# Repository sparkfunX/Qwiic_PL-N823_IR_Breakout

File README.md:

SparkFun PL-N823 IR Breakout
===================================

[*SparkFun Qwiic IR Breakout (SPX-15804)*](https://www.sparkfun.com/products/15804)

PL-N823-01 Lensless IR Sensor breakout with signal amplifier and I2C ADC 

This board allows for digital sensor reading of IR signals from external sources. One such application can be the detection of heat given off by the human body. Operating voltage is 5V for the board as a whole, and while under 1mm thick materials detection can be as far away as 10cm to 20cm.

Repository contents
-------------------

* **/Documents** - Contains datasheets
* **/Hardware** - Current .brd and .sch files for product

Documentation
-------------

* **[Installing an Arduino Library Guide](https://learn.sparkfun.com/tutorials/installing-an-arduino-library)** - Basic information on how to install an Arduino library.

License Information
-------------------

This product is _**open source**_!

Please review the LICENSE.md file for license information.

If you have any questions or concerns on licensing, please contact technical support on our [SparkFun forums](https://forum.sparkfun.com/viewforum.php?f=152).

Distributed as-is; no warranty is given.

- Your friends at SparkFun.

_<COLLABORATION CREDIT>_

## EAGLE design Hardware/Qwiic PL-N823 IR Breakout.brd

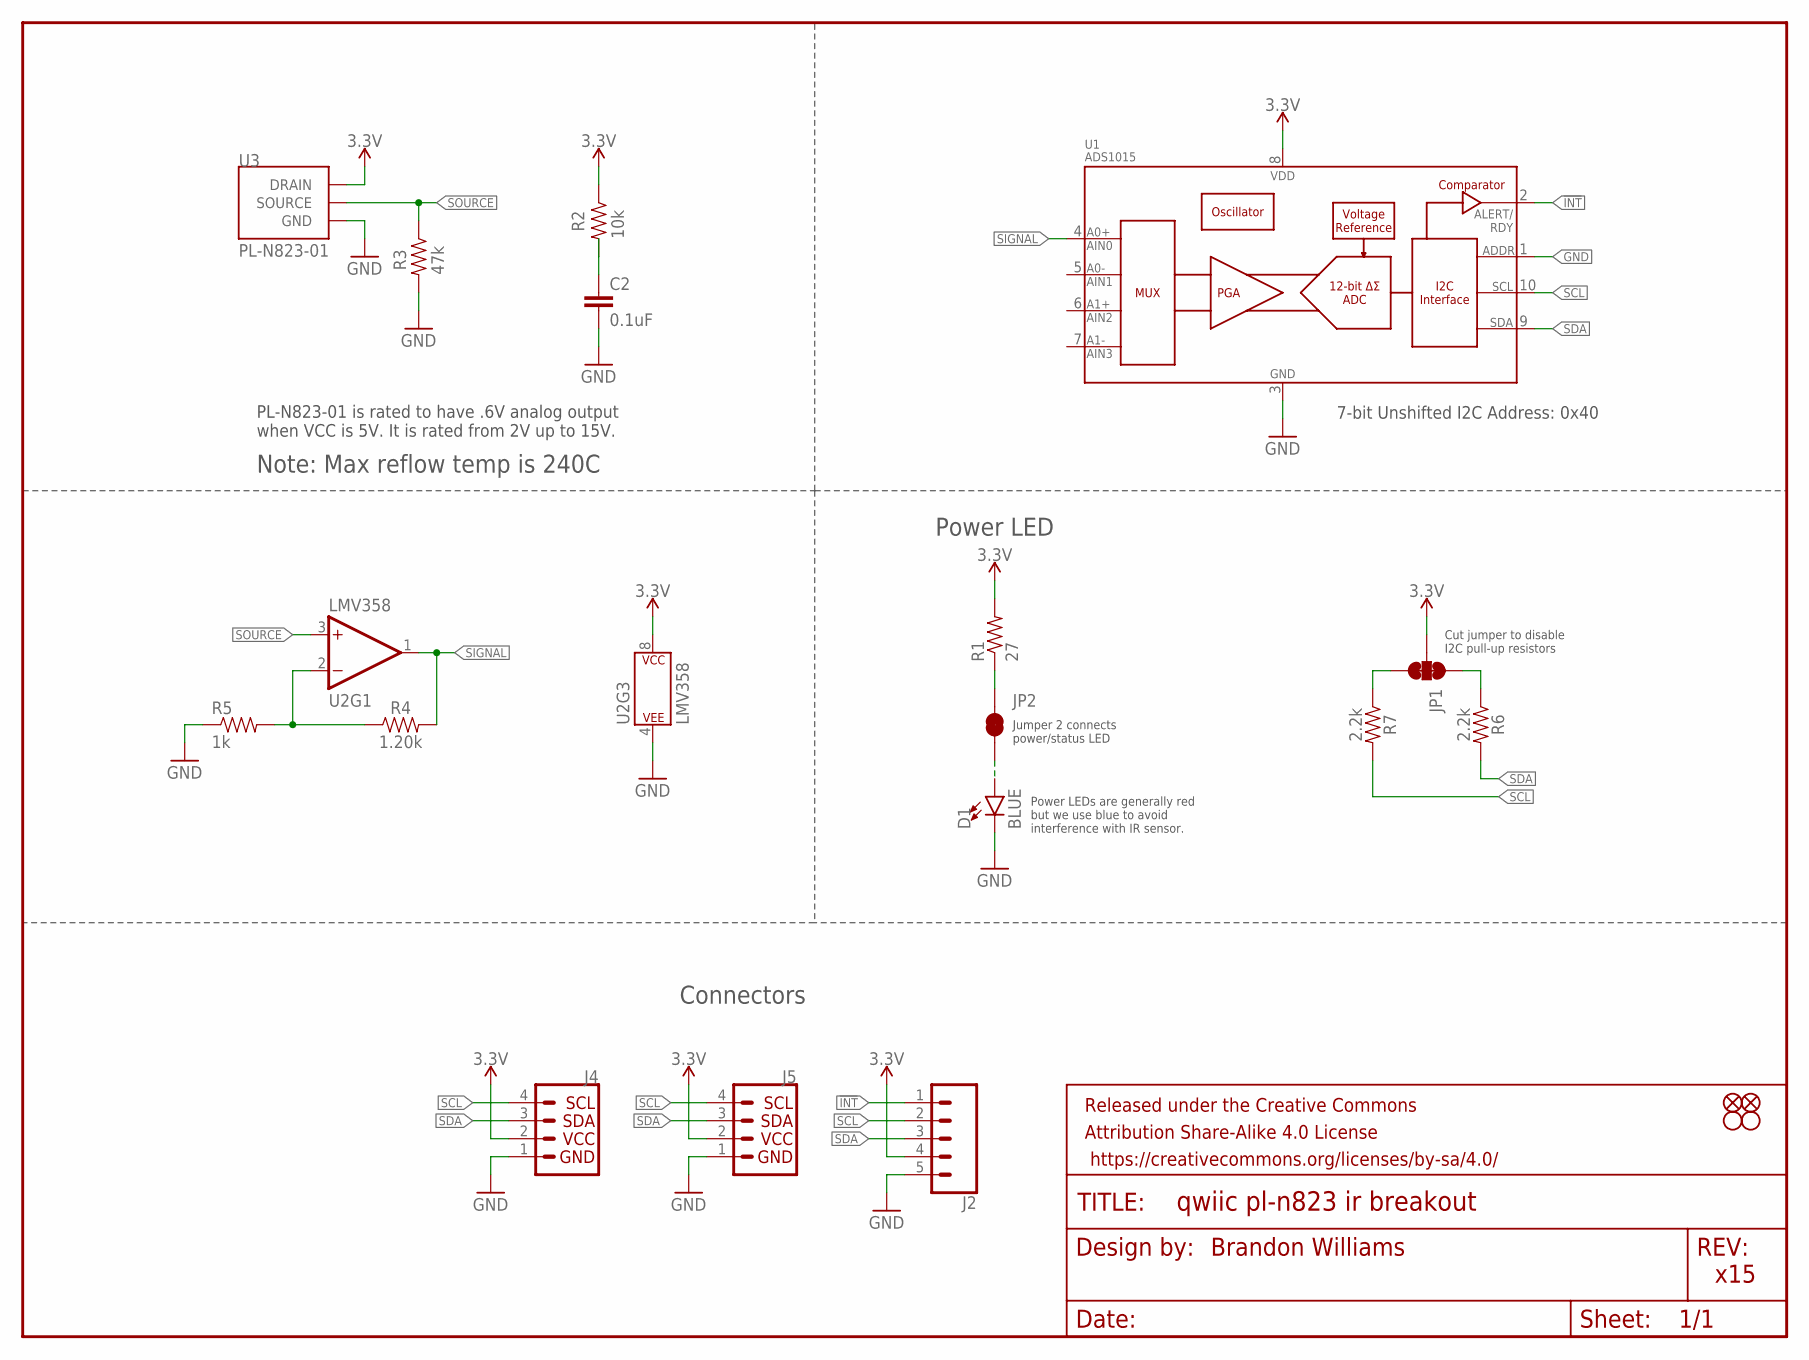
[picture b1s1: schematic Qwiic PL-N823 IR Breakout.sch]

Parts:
C2: 0.1uF; 0603
D1: BLUE; LED-0603
FD1, FD2: FIDUCIALUFIDUCIAL; FIDUCIAL-MICRO
FRAME1: FRAME-LETTERNO_PACKAGE; DUMMY
H1, H2: STAND-OFFTIGHT; STAND-OFF-TIGHT
J2: CONN_05NO_SILK; 1X05_NO_SILK
J4, J5: QWIIC_CONNECTORJS-1MM; JST04_1MM_RA
JP1: JUMPER-SMT_3_2-NC_TRACE_SILK; SMT-JUMPER_3_2-NC_TRACE_SILK
JP2: JUMPER-SMT_2_NC_TRACE_SILK; SMT-JUMPER_2_NC_TRACE_SILK
R1: 27; 0603
R2: 10k; 0603
R3: 47k; 0603
R4: 1.20k; 0603
R5: 1k; 0603
R6, R7: 2.2k; 0603
U1: ADS1015; MSOP10
U2: LMV358; SO08
U3: PL-N823-01

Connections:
3.3V: J2.4, J4.2, J5.2, JP1.2, R1.2, R2.1, U1.8 (VDD), U2.8 (P$V+), U3.DRAIN
!INT: J2.1, U1.2 (ALERT/RDY)
GND: C2.2, D1.C, J2.5, J4.1, J5.1, R3.2, R5.1, U1.1 (ADDR), U1.3 (VSS), U2.4 (P$V-), U3.GND@1 (GND), U3.GND@2 (GND)
unnamed: R4.1, R5.2, U2.2 (-IN)
unnamed: C2.1, R2.2
unnamed: JP2.1, R1.1
unnamed: JP1.3, R7.1
unnamed: JP1.1, R6.1
unnamed: D1.A, JP2.2
SCL: J2.2, J4.4, J5.4, R7.2, U1.10 (SCL)
SDA: J2.3, J4.3, J5.3, R6.2, U1.9 (SDA)
SIGNAL: R4.2, U1.4 (AIN0), U2.1 (OUT)
SOURCE: R3.1, U2.3 (+IN), U3.SOURCE

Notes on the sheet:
Brandon Williams
x15
7-bit Unshifted I2C Address: 0x40
Power LED
Jumper 2 connects power/status LED
Cut jumper to disable I2C pull-up resistors
PL-N823-01 is rated to have .6V analog output when VCC is 5V. It is rated from 2V up to 15V.
Connectors
Note: Max reflow temp is 240C
Power LEDs are generally red but we use blue to avoid interference with IR sensor.

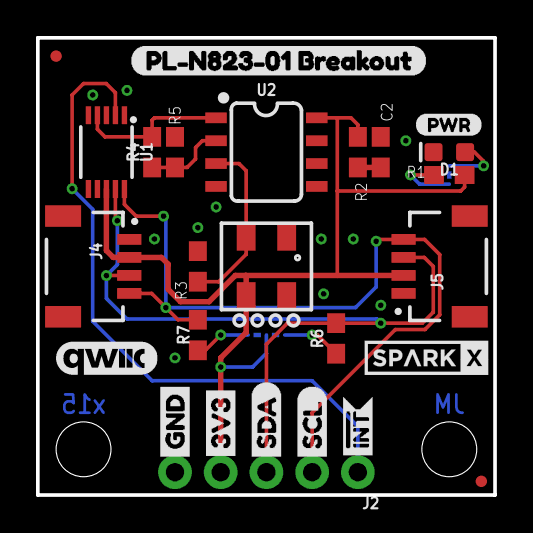
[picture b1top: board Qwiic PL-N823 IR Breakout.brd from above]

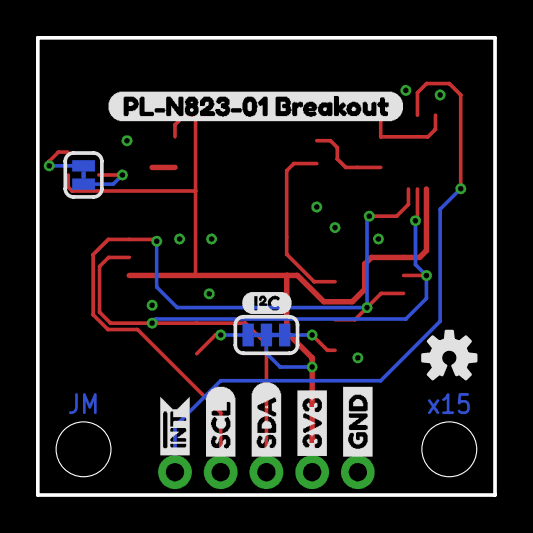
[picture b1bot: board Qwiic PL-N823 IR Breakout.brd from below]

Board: 2 copper layers, 25.4 x 25.4 mm, 40 parts (10 on the bottom side), 13 nets.

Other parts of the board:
U$1: QWIIC_COPYRIGHT_SMALL
U$2, U$13: SDA-[)
U$3: PRODUCTION_INSTRUCTIONS
U$4, U$8: PL#N823#01_BREAKOUT0
U$5: I_SUPER2_C-()-03
U$6, U$11: INT#-[<-04
U$7: OSHW-LOGO-S
U$9: PWR-()-03
U$10: SPARKX-SMALL
U$12, U$14: SCL-[)
U$15, U$16: 3V3-04
U$17, U$18: GND-04

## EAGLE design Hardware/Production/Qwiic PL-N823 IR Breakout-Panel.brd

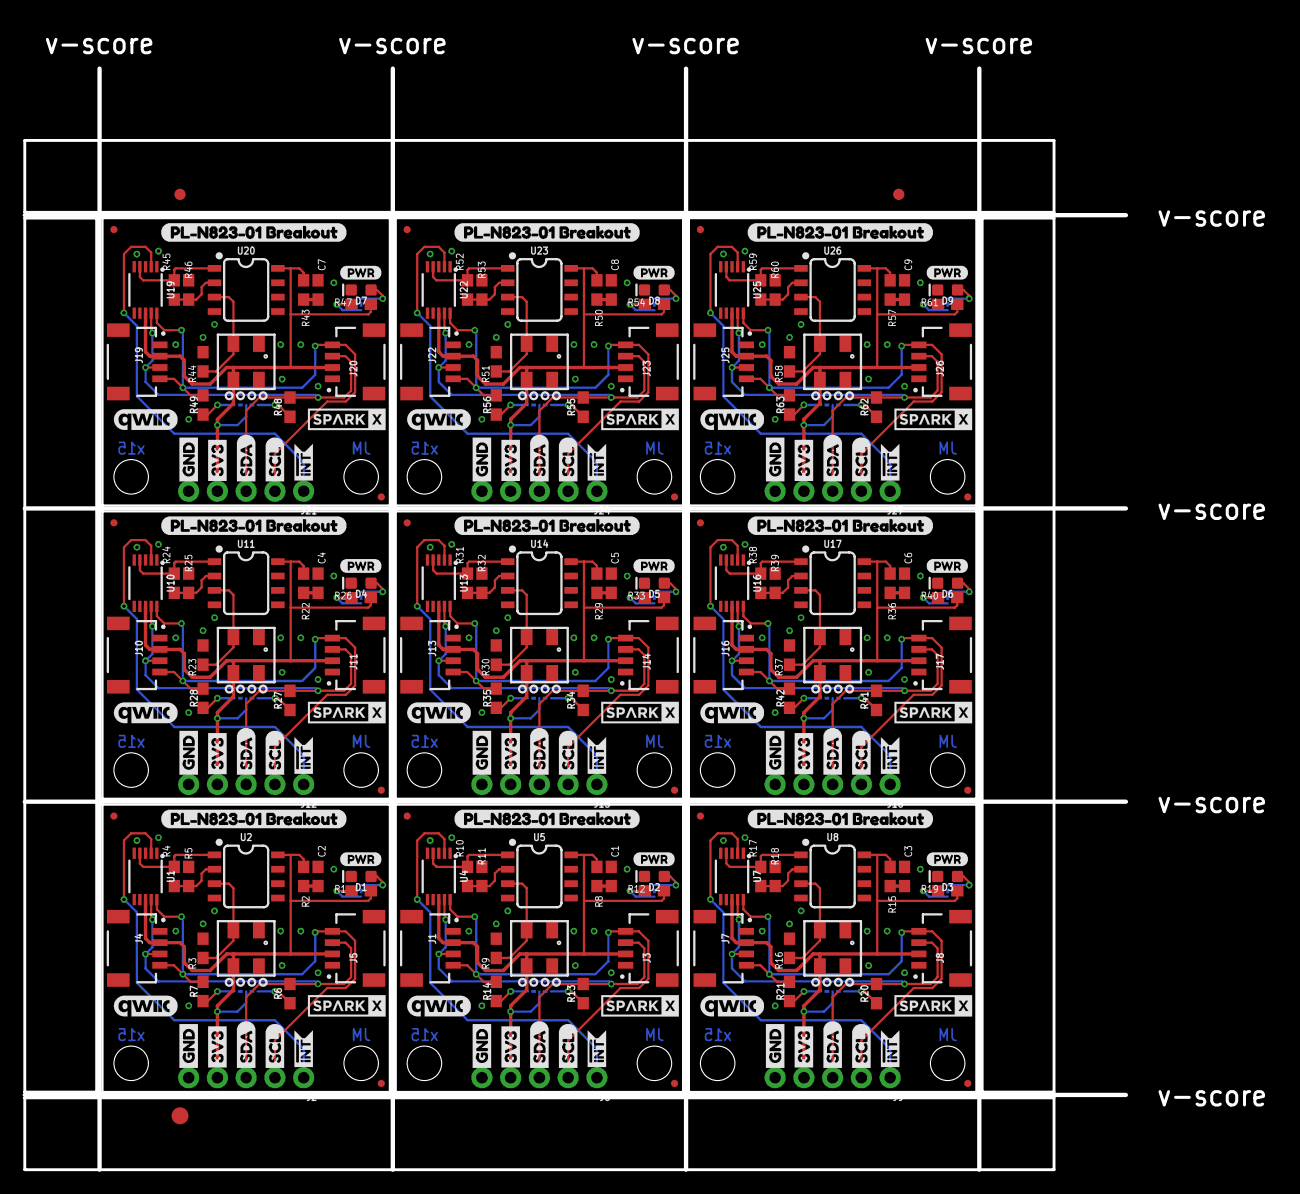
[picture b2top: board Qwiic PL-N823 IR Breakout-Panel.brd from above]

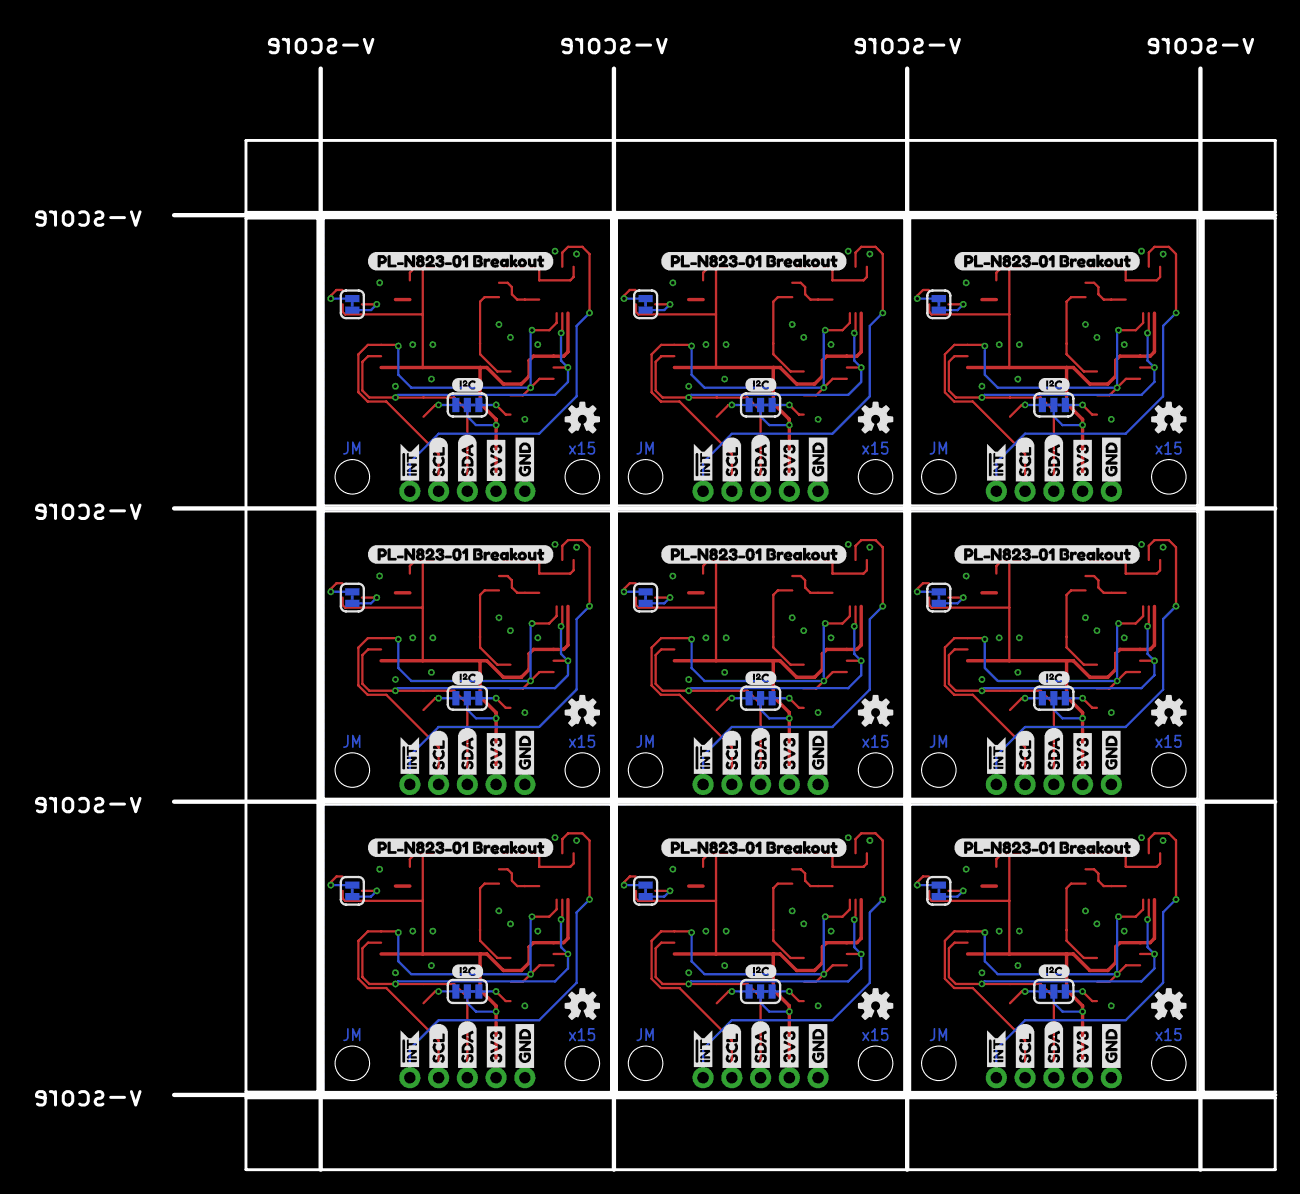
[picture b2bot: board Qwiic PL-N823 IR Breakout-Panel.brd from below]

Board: 2 copper layers, 110.5 x 101.2 mm, 354 parts (90 on the bottom side), 117 nets.

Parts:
C1, C2, C3, C4, C5, C6, C7, C8, C9: 0.1uF; 0603
D1, D2, D3, D4, D5, D6, D7, D8, D9: RED; LED-0603
E$1, E$2: FIDUCIAL-1X2
E$3: FIDUCIAL-1.5X3
FD1, FD2, FD3, FD4, FD5, FD6, FD7, FD8, FD9, FD10, FD11, FD12, FD13, FD14, FD15, FD16, FD17, FD18: FIDUCIALUFIDUCIAL; FIDUCIAL-MICRO
FRAME1, FRAME2, FRAME3, FRAME4, FRAME5, FRAME6, FRAME7, FRAME8, FRAME9: FRAME-LETTERNO_PACKAGE; DUMMY
H1, H2, H3, H4, H5, H6, H7, H8, H9, H10, H11, H12, H13, H14, H15, H16, H17, H18: STAND-OFFTIGHT; STAND-OFF-TIGHT
J1, J3, J4, J5, J7, J8, J10, J11, J13, J14, J16, J17, J19, J20, J22, J23, J25, J26: JST04_1MM_RA
J2, J6, J9, J12, J15, J18, J21, J24, J27: 1X05_NO_SILK
JP1, JP3, JP5, JP7, JP9, JP11, JP13, JP15, JP17: JUMPER-SMT_3_2-NC_TRACE_SILK; SMT-JUMPER_3_2-NC_TRACE_SILK
JP2, JP4, JP6, JP8, JP10, JP12, JP14, JP16, JP18: JUMPER-SMT_2_NC_TRACE_SILK; SMT-JUMPER_2_NC_TRACE_SILK
R1, R12, R19, R26, R33, R40, R47, R54, R61: 27; 0603
R2, R8, R15, R22, R29, R36, R43, R50, R57: 10k; 0603
R3, R9, R16, R23, R30, R37, R44, R51, R58: 47k; 0603
R4, R10, R17, R24, R31, R38, R45, R52, R59: 4.7k; 0603
R5, R11, R18, R25, R32, R39, R46, R53, R60: 1k; 0603
R6, R7, R13, R14, R20, R21, R27, R28, R34, R35, R41, R42, R48, R49, R55, R56, R62, R63: 2.2k; 0603
U1, U4, U7, U10, U13, U16, U19, U22, U25: ADS1015; MSOP10
U2, U5, U8, U11, U14, U17, U20, U23, U26: LMV358; SO08
U3, U6, U9, U12, U15, U18, U21, U24, U27: PL-N823-01
U$1, U$21, U$38, U$55, U$72, U$89, U$106, U$123, U$140: QWIIC_COPYRIGHT_SMALL
U$2, U$13, U$23, U$25, U$40, U$42, U$57, U$59, U$74, U$76, U$91, U$93, U$108, U$110, U$125, U$127, U$142, U$144: SDA-[)
U$3, U$7, U$35, U$52, U$69, U$86, U$103, U$120, U$137: OSHW-LOGO-S
U$4, U$8, U$19, U$31, U$36, U$48, U$53, U$65, U$70, U$82, U$87, U$99, U$104, U$116, U$121, U$133, U$138, U$150: PL#N823#01_BREAKOUT0
U$5, U$32, U$49, U$66, U$83, U$100, U$117, U$134, U$151: I_SUPER2_C-()-03
U$6, U$11, U$33, U$34, U$50, U$51, U$67, U$68, U$84, U$85, U$101, U$102, U$118, U$119, U$135, U$136, U$152, U$153: INT#-[<-04
U$9, U$22, U$39, U$56, U$73, U$90, U$107, U$124, U$141: PWR-()-03
U$10, U$20, U$37, U$54, U$71, U$88, U$105, U$122, U$139: SPARKX-SMALL
U$12, U$14, U$24, U$26, U$41, U$43, U$58, U$60, U$75, U$77, U$92, U$94, U$109, U$111, U$126, U$128, U$143, U$145: SCL-[)
U$15, U$16, U$27, U$28, U$44, U$45, U$61, U$62, U$78, U$79, U$95, U$96, U$112, U$113, U$129, U$130, U$146, U$147: 3V3-04
U$17, U$18, U$29, U$30, U$46, U$47, U$63, U$64, U$80, U$81, U$97, U$98, U$114, U$115, U$131, U$132, U$148, U$149: GND-04

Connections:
3.3V: J2.4, J4.2, J5.2, JP1.2, R1.2, R2.1, U1.8, U2.8, U3.DRAIN
3.3V1: J1.2, J3.2, J6.4, JP3.2, R8.1, R12.2, U4.8, U5.8, U6.DRAIN
3.3V2: J7.2, J8.2, J9.4, JP5.2, R15.1, R19.2, U7.8, U8.8, U9.DRAIN
3.3V3: J10.2, J11.2, J12.4, JP7.2, R22.1, R26.2, U10.8, U11.8, U12.DRAIN
3.3V4: J13.2, J14.2, J15.4, JP9.2, R29.1, R33.2, U13.8, U14.8, U15.DRAIN
3.3V5: J16.2, J17.2, J18.4, JP11.2, R36.1, R40.2, U16.8, U17.8, U18.DRAIN
3.3V6: J19.2, J20.2, J21.4, JP13.2, R43.1, R47.2, U19.8, U20.8, U21.DRAIN
3.3V7: J22.2, J23.2, J24.4, JP15.2, R50.1, R54.2, U22.8, U23.8, U24.DRAIN
3.3V8: J25.2, J26.2, J27.4, JP17.2, R57.1, R61.2, U25.8, U26.8, U27.DRAIN
!INT: J2.1, U1.2
!INT1: J6.1, U4.2
!INT2: J9.1, U7.2
!INT3: J12.1, U10.2
!INT4: J15.1, U13.2
!INT5: J18.1, U16.2
!INT6: J21.1, U19.2
!INT7: J24.1, U22.2
!INT8: J27.1, U25.2
GND: C2.2, D1.C, J2.5, J4.1, J5.1, R3.2, R5.1, U1.1, U1.3, U2.4, U3.GND@1, U3.GND@2
GND1: C1.2, D2.C, J1.1, J3.1, J6.5, R9.2, R11.1, U4.1, U4.3, U5.4, U6.GND@1, U6.GND@2
GND2: C3.2, D3.C, J7.1, J8.1, J9.5, R16.2, R18.1, U7.1, U7.3, U8.4, U9.GND@1, U9.GND@2
GND3: C4.2, D4.C, J10.1, J11.1, J12.5, R23.2, R25.1, U10.1, U10.3, U11.4, U12.GND@1, U12.GND@2
GND4: C5.2, D5.C, J13.1, J14.1, J15.5, R30.2, R32.1, U13.1, U13.3, U14.4, U15.GND@1, U15.GND@2
GND5: C6.2, D6.C, J16.1, J17.1, J18.5, R37.2, R39.1, U16.1, U16.3, U17.4, U18.GND@1, U18.GND@2
GND6: C7.2, D7.C, J19.1, J20.1, J21.5, R44.2, R46.1, U19.1, U19.3, U20.4, U21.GND@1, U21.GND@2
GND7: C8.2, D8.C, J22.1, J23.1, J24.5, R51.2, R53.1, U22.1, U22.3, U23.4, U24.GND@1, U24.GND@2
GND8: C9.2, D9.C, J25.1, J26.1, J27.5, R58.2, R60.1, U25.1, U25.3, U26.4, U27.GND@1, U27.GND@2
unnamed: R4.1, R5.2, U2.2
unnamed: C2.1, R2.2
unnamed: JP2.1, R1.1
unnamed: JP1.3, R7.1
unnamed: JP1.1, R6.1
unnamed: D1.A, JP2.2
unnamed: C1.1, R8.2
unnamed: R10.1, R11.2, U5.2
unnamed: JP3.3, R14.1
unnamed: JP3.1, R13.1
unnamed: D2.A, JP4.2
unnamed: JP4.1, R12.1
unnamed: C3.1, R15.2
unnamed: R17.1, R18.2, U8.2
unnamed: JP5.3, R21.1
unnamed: JP5.1, R20.1
unnamed: D3.A, JP6.2
unnamed: JP6.1, R19.1
unnamed: C4.1, R22.2
unnamed: R24.1, R25.2, U11.2
unnamed: JP7.3, R28.1
unnamed: JP7.1, R27.1
unnamed: D4.A, JP8.2
unnamed: JP8.1, R26.1
unnamed: C5.1, R29.2
unnamed: R31.1, R32.2, U14.2
unnamed: JP9.3, R35.1
unnamed: JP9.1, R34.1
unnamed: D5.A, JP10.2
unnamed: JP10.1, R33.1
unnamed: C6.1, R36.2
unnamed: R38.1, R39.2, U17.2
unnamed: JP11.3, R42.1
unnamed: JP11.1, R41.1
unnamed: D6.A, JP12.2
unnamed: JP12.1, R40.1
unnamed: C7.1, R43.2
unnamed: R45.1, R46.2, U20.2
unnamed: JP13.3, R49.1
unnamed: JP13.1, R48.1
unnamed: D7.A, JP14.2
unnamed: JP14.1, R47.1
unnamed: C8.1, R50.2
unnamed: R52.1, R53.2, U23.2
unnamed: JP15.3, R56.1
unnamed: JP15.1, R55.1
unnamed: D8.A, JP16.2
unnamed: JP16.1, R54.1
unnamed: C9.1, R57.2
unnamed: R59.1, R60.2, U26.2
unnamed: JP17.3, R63.1
unnamed: JP17.1, R62.1
unnamed: D9.A, JP18.2
unnamed: JP18.1, R61.1
SCL: J2.2, J4.4, J5.4, R7.2, U1.10
SCL1: J1.4, J3.4, J6.2, R14.2, U4.10
SCL2: J7.4, J8.4, J9.2, R21.2, U7.10
SCL3: J10.4, J11.4, J12.2, R28.2, U10.10
SCL4: J13.4, J14.4, J15.2, R35.2, U13.10
SCL5: J16.4, J17.4, J18.2, R42.2, U16.10
SCL6: J19.4, J20.4, J21.2, R49.2, U19.10
SCL7: J22.4, J23.4, J24.2, R56.2, U22.10
SCL8: J25.4, J26.4, J27.2, R63.2, U25.10
SDA: J2.3, J4.3, J5.3, R6.2, U1.9
SDA1: J1.3, J3.3, J6.3, R13.2, U4.9
SDA2: J7.3, J8.3, J9.3, R20.2, U7.9
SDA3: J10.3, J11.3, J12.3, R27.2, U10.9
SDA4: J13.3, J14.3, J15.3, R34.2, U13.9
SDA5: J16.3, J17.3, J18.3, R41.2, U16.9
SDA6: J19.3, J20.3, J21.3, R48.2, U19.9
SDA7: J22.3, J23.3, J24.3, R55.2, U22.9
SDA8: J25.3, J26.3, J27.3, R62.2, U25.9
SIGNAL: R4.2, U1.4, U2.1
SIGNAL1: R10.2, U4.4, U5.1
SIGNAL2: R17.2, U7.4, U8.1
SIGNAL3: R24.2, U10.4, U11.1
SIGNAL4: R31.2, U13.4, U14.1
SIGNAL5: R38.2, U16.4, U17.1
SIGNAL6: R45.2, U19.4, U20.1
SIGNAL7: R52.2, U22.4, U23.1
SIGNAL8: R59.2, U25.4, U26.1
SOURCE: R3.1, U2.3, U3.SOURCE
SOURCE1: R9.1, U5.3, U6.SOURCE
SOURCE2: R16.1, U8.3, U9.SOURCE
SOURCE3: R23.1, U11.3, U12.SOURCE
SOURCE4: R30.1, U14.3, U15.SOURCE
SOURCE5: R37.1, U17.3, U18.SOURCE
SOURCE6: R44.1, U20.3, U21.SOURCE
SOURCE7: R51.1, U23.3, U24.SOURCE
SOURCE8: R58.1, U26.3, U27.SOURCE

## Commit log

2019-06-11 Add panel
2019-06-11 Add no clean note. Change to blue power LED.
2019-11-18 Updated amplifier circuit
2019-11-22 New panel and output files with correct amp circuit
    Changed amplification gain factor
2019-12-02 Transition to production: Added PROD_ID of IR sensor

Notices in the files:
parts and their libraries:
SparkFun-Aesthetics: Licensing: Creative Commons ShareAlike 4.0 International - https://creativecommons.org/licenses/by-sa/4.0
SparkFun-Aesthetics: Released under the Creative Commons Attribution Share-Alike 4.0 License
SparkFun-Aesthetics: https://creativecommons.org/licenses/by-sa/4.0
